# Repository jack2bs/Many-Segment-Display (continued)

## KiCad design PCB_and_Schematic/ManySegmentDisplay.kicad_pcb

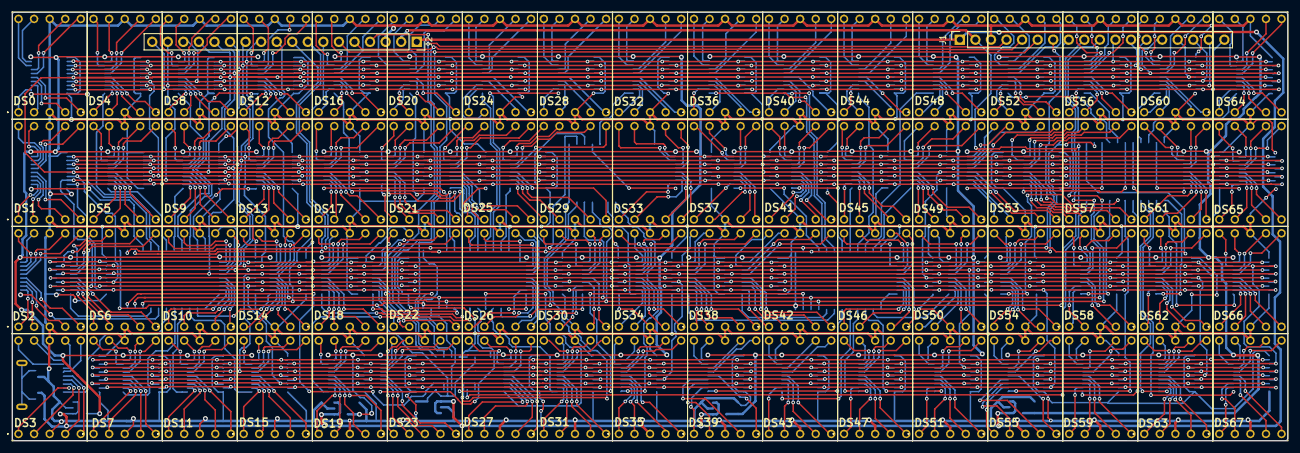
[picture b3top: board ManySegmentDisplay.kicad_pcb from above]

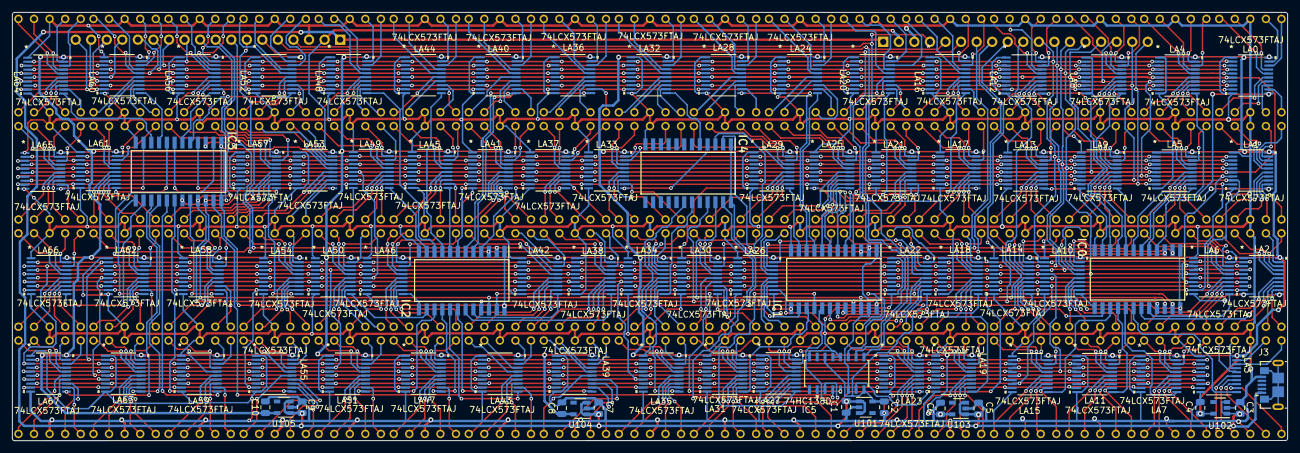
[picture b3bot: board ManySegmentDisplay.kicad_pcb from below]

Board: 2 copper layers, 208.1 x 69.9 mm, 160 parts (90 on the bottom side), 636 nets.

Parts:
C1, C2, C3, C4, C5, C6, C7, C8, C9, C10: 1uF; C_0805_2012Metric
DS0, DS1, DS2, DS3, DS4, DS5, DS6, DS7, DS8, DS9, DS10, DS11, DS12, DS13, DS14, DS15, DS16, DS17, DS18, DS19, DS20, DS21, DS22, DS23, DS24, DS25, DS26, DS27, DS28, DS29, DS30, DS31, DS32, DS33, DS34, DS35, DS36, DS37, DS38, DS39, DS40, DS41, DS42, DS43, DS44, DS45, DS46, DS47, DS48, DS49, DS50, DS51, DS52, DS53, DS54, DS55, DS56, DS57, DS58, DS59, DS60, DS61, DS62, DS63, DS64, DS65, DS66, DS67: TDSR1360-IK; TDSR1360IK
IC0, IC1, IC2, IC3, IC4: 74HC4514D,653; SOIC127P1032X265-24N
IC5: 74HC138D
J1, J2: ManySegDisplayConn; PinSocket_1x18_P2.54mm_Vertical
J3: USB_B_Micro; USB_Micro-B_GCT_USB3076-30-A
LA0, LA1, LA2, LA3, LA4, LA5, LA6, LA7, LA8, LA9, LA10, LA11, LA12, LA13, LA14, LA15, LA16, LA17, LA18, LA19, LA20, LA21, LA22, LA23, LA24, LA25, LA26, LA27, LA28, LA29, LA30, LA31, LA32, LA33, LA34, LA35, LA36, LA37, LA38, LA39, LA40, LA41, LA42, LA43, LA44, LA45, LA46, LA47, LA48, LA49, LA50, LA51, LA52, LA53, LA54, LA55, LA56, LA57, LA58, LA59, LA60, LA61, LA62, LA63, LA64, LA65, LA66, LA67: 74LCX573FTAJ
U101, U102, U103, U104, U105: TPS73133DBV; SOT-23-5

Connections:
+1V8: C4.1, C6.1, C8.1, C10.1, LA0.20, LA1.20, LA2.20, LA3.20, LA4.20, LA5.20, LA6.20, LA7.20, LA8.20, LA9.20, LA10.20, LA11.20, LA12.20, LA13.20, LA14.20, LA15.20, LA16.20, LA17.20, LA18.20, LA19.20, LA20.20, LA21.20, LA22.20, LA23.20, LA24.20, LA25.20, LA26.20, LA27.20, LA28.20, LA29.20, LA30.20, LA31.20, LA32.20, LA33.20, LA34.20, LA35.20, LA36.20, LA37.20, LA38.20, LA39.20, LA40.20, LA41.20, LA42.20, LA43.20, LA44.20, LA45.20, LA46.20, LA47.20, LA48.20, LA49.20, LA50.20, LA51.20, LA52.20, LA53.20, LA54.20, LA55.20, LA56.20, LA57.20, LA58.20, LA59.20, LA60.20, LA61.20, LA62.20, LA63.20, LA64.20, LA65.20, LA66.20, LA67.20, U102.5, U103.5, U104.5, U105.5
+3V3: C2.1, IC0.1, IC0.24, IC1.1, IC1.24, IC2.1, IC2.24, IC3.1, IC3.24, IC4.1, IC4.24, IC5.6, IC5.16, J1.2, J2.2, U101.5
+5V: C1.1, C3.1, C5.1, C7.1, C9.1, J1.1, J2.1, J3.1, U101.1, U101.3, U102.1, U102.3, U103.1, U103.3, U104.1, U104.3, U105.1, U105.3
AD0: IC5.1, J1.4, J2.4
AD1: IC5.2, J1.5, J2.5
AD2: IC5.3, J1.6, J2.6
AD3: IC0.2, IC1.2, IC2.2, IC3.2, IC4.2, J1.7, J2.7
AD4: IC0.3, IC1.3, IC2.3, IC3.3, IC4.3, J1.8, J2.8
AD5: IC0.21, IC1.21, IC2.21, IC3.21, IC4.21, J1.9, J2.9
AD6: IC0.22, IC1.22, IC2.22, IC3.22, IC4.22, J1.10, J2.10
D1A: IC0.13, LA10.11
D1B: IC0.16, LA11.11
D1C: IC0.10, LA12.11
D1D: IC0.11, LA13.11
D1E: IC0.14, LA14.11
D1F: IC0.15, LA15.11
D2A: IC1.13, LA26.11
D2B: IC1.16, LA27.11
D2C: IC1.10, LA28.11
D2D: IC1.11, LA29.11
D2E: IC1.14, LA30.11
D2F: IC1.15, LA31.11
D3A: IC2.13, LA46.11
D3B: IC2.16, LA47.11
D3C: IC2.10, LA48.11
D3D: IC2.11, LA49.11
D3E: IC2.14, LA50.11
D3F: IC2.15, LA51.11
D4A: IC3.13, LA62.11
D4B: IC3.16, LA63.11
D4C: IC3.10, LA64.11
D4D: IC3.11, LA65.11
D4E: IC3.14, LA66.11
D4F: IC3.15, LA67.11
D10: IC0.5, LA0.11
D11: IC0.4, LA1.11
D12: IC0.19, LA2.11
D13: IC0.18, LA3.11
D14: IC0.6, LA4.11
D15: IC0.7, LA5.11
D16: IC0.20, LA6.11
D17: IC0.17, LA7.11
D18: IC0.9, LA8.11
D19: IC0.8, LA9.11
D20: IC1.5, LA16.11
D21: IC1.4, LA17.11
D22: IC1.19, LA18.11
D23: IC1.18, LA19.11
D24: IC1.6, LA20.11
D25: IC1.7, LA21.11
D26: IC1.20, LA22.11
D27: IC1.17, LA23.11
D28: IC1.9, LA24.11
D29: IC1.8, LA25.11
D30: IC2.5, LA36.11
D31: IC2.4, LA37.11
D32: IC2.19, LA38.11
D33: IC2.18, LA39.11
D34: IC2.6, LA40.11
D35: IC2.7, LA41.11
D36: IC2.20, LA42.11
D37: IC2.17, LA43.11
D38: IC2.9, LA44.11
D39: IC2.8, LA45.11
D40: IC3.5, LA52.11
D41: IC3.4, LA53.11
D42: IC3.19, LA54.11
D43: IC3.18, LA55.11
D44: IC3.6, LA56.11
D45: IC3.7, LA57.11
D46: IC3.20, LA58.11
D47: IC3.17, LA59.11
D48: IC3.9, LA60.11
D49: IC3.8, LA61.11
D50: IC4.5, LA32.11
D51: IC4.4, LA33.11
D52: IC4.19, LA34.11
D53: IC4.18, LA35.11
GND: C1.2, C2.2, C3.2, C4.2, C5.2, C6.2, C7.2, C8.2, C9.2, C10.2, DS0.3, DS0.8, DS1.3, DS1.8, DS2.3, DS2.8, DS3.3, DS3.8, DS4.3, DS4.8, DS5.3, DS5.8, DS6.3, DS6.8, DS7.3, DS7.8, DS8.3, DS8.8, DS9.3, DS9.8, DS10.3, DS10.8, DS11.3, DS11.8, DS12.3, DS12.8, DS13.3, DS13.8, DS14.3, DS14.8, DS15.3, DS15.8, DS16.3, DS16.8, DS17.3, DS17.8, DS18.3, DS18.8, DS19.3, DS19.8, DS20.3, DS20.8, DS21.3, DS21.8, DS22.3, DS22.8, DS23.3, DS23.8, DS24.3, DS24.8, DS25.3, DS25.8, DS26.3, DS26.8, DS27.3, DS27.8, DS28.3, DS28.8, DS29.3, DS29.8, DS30.3, DS30.8, DS31.3, DS31.8, DS32.3, DS32.8, DS33.3, DS33.8, DS34.3, DS34.8, DS35.3, DS35.8, DS36.3, DS36.8, DS37.3, DS37.8, DS38.3, DS38.8, DS39.3, DS39.8, DS40.3, DS40.8, DS41.3, DS41.8, DS42.3, DS42.8, DS43.3, DS43.8, DS44.3, DS44.8, DS45.3, DS45.8, DS46.3, DS46.8, DS47.3, DS47.8, DS48.3, DS48.8, DS49.3, DS49.8, DS50.3, DS50.8, DS51.3, DS51.8, DS52.3, DS52.8, DS53.3, DS53.8, DS54.3, DS54.8, DS55.3, DS55.8, DS56.3, DS56.8, DS57.3, DS57.8, DS58.3, DS58.8, DS59.3, DS59.8, DS60.3, DS60.8, DS61.3, DS61.8, DS62.3, DS62.8, DS63.3, DS63.8, DS64.3, DS64.8, DS65.3, DS65.8, DS66.3, DS66.8, DS67.3, DS67.8, IC0.12, IC1.12, IC2.12, IC3.12, IC4.12, IC5.4, IC5.5, IC5.8, J1.3, J2.3, J3.5, LA0.1, LA0.10, LA1.1, LA1.10, LA2.1, LA2.10, LA3.1, LA3.10, LA4.1, LA4.10, LA5.1, LA5.10, LA6.1, LA6.10, LA7.1, LA7.10, LA8.1, LA8.10, LA9.1, LA9.10, LA10.1, LA10.10, LA11.1, LA11.10, LA12.1, LA12.10, LA13.1, LA13.10, LA14.1, LA14.10, LA15.1, LA15.10, LA16.1, LA16.10, LA17.1, LA17.10, LA18.1, LA18.10, LA19.1, LA19.10, LA20.1, LA20.10, LA21.1, LA21.10, LA22.1, LA22.10, LA23.1, LA23.10, LA24.1, LA24.10, LA25.1, LA25.10, LA26.1, LA26.10, LA27.1, LA27.10, LA28.1, LA28.10, LA29.1, LA29.10, LA30.1, LA30.10, LA31.1, LA31.10, LA32.1, LA32.10, LA33.1, LA33.10, LA34.1, LA34.10, LA35.1, LA35.10, LA36.1, LA36.10, LA37.1, LA37.10, LA38.1, LA38.10, LA39.1, LA39.10, LA40.1, LA40.10, LA41.1, LA41.10, LA42.1, LA42.10, LA43.1, LA43.10, LA44.1, LA44.10, LA45.1, LA45.10, LA46.1, LA46.10, LA47.1, LA47.10, LA48.1, LA48.10, LA49.1, LA49.10, LA50.1, LA50.10, LA51.1, LA51.10, LA52.1, LA52.10, LA53.1, LA53.10, LA54.1, LA54.10, LA55.1, LA55.10, LA56.1, LA56.10, LA57.1, LA57.10, LA58.1, LA58.10, LA59.1, LA59.10, LA60.1, LA60.10, LA61.1, LA61.10, LA62.1, LA62.10, LA63.1, LA63.10, LA64.1, LA64.10, LA65.1, LA65.10, LA66.1, LA66.10, LA67.1, LA67.10, U101.2, U102.2, U103.2, U104.2, U105.2
unnamed: DS0.1, LA0.12
unnamed: DS0.2, LA0.13
unnamed: DS0.4, LA0.14
unnamed: DS0.5, LA0.15
unnamed: DS0.6, LA0.16
unnamed: DS0.7, LA0.17
unnamed: DS0.9, LA0.19
unnamed: DS0.10, LA0.18
unnamed: DS1.1, LA1.12
unnamed: DS1.2, LA1.13
unnamed: DS1.4, LA1.14
unnamed: DS1.5, LA1.15
unnamed: DS1.6, LA1.16
unnamed: DS1.7, LA1.17
unnamed: DS1.9, LA1.19
unnamed: DS1.10, LA1.18
unnamed: DS2.1, LA2.12
unnamed: DS2.2, LA2.13
unnamed: DS2.4, LA2.14
unnamed: DS2.5, LA2.15
unnamed: DS2.6, LA2.16
unnamed: DS2.7, LA2.17
unnamed: DS2.9, LA2.19
unnamed: DS2.10, LA2.18
unnamed: DS3.1, LA3.12
unnamed: DS3.2, LA3.13
unnamed: DS3.4, LA3.14
unnamed: DS3.5, LA3.15
unnamed: DS3.6, LA3.16
unnamed: DS3.7, LA3.17
unnamed: DS3.9, LA3.19
unnamed: DS3.10, LA3.18
unnamed: DS4.1, LA4.12
unnamed: DS4.2, LA4.13
unnamed: DS4.4, LA4.14
unnamed: DS4.5, LA4.15
unnamed: DS4.6, LA4.16
unnamed: DS4.7, LA4.17
unnamed: DS4.9, LA4.19
unnamed: DS4.10, LA4.18
unnamed: DS5.1, LA5.12
unnamed: DS5.2, LA5.13
unnamed: DS5.4, LA5.14
unnamed: DS5.5, LA5.15
unnamed: DS5.6, LA5.16
unnamed: DS5.7, LA5.17
unnamed: DS5.9, LA5.19
unnamed: DS5.10, LA5.18
unnamed: DS6.1, LA6.12
unnamed: DS6.2, LA6.13
unnamed: DS6.4, LA6.14
unnamed: DS6.5, LA6.15
unnamed: DS6.6, LA6.16
unnamed: DS6.7, LA6.17
unnamed: DS6.9, LA6.19
unnamed: DS6.10, LA6.18
unnamed: DS7.1, LA7.12
unnamed: DS7.2, LA7.13
unnamed: DS7.4, LA7.14
unnamed: DS7.5, LA7.15
unnamed: DS7.6, LA7.16
unnamed: DS7.7, LA7.17
unnamed: DS7.9, LA7.19
unnamed: DS7.10, LA7.18
unnamed: DS8.1, LA8.12
unnamed: DS8.2, LA8.13
unnamed: DS8.4, LA8.14
unnamed: DS8.5, LA8.15
unnamed: DS8.6, LA8.16
unnamed: DS8.7, LA8.17
unnamed: DS8.9, LA8.19
unnamed: DS8.10, LA8.18
unnamed: DS9.1, LA9.12
unnamed: DS9.2, LA9.13
unnamed: DS9.4, LA9.14
unnamed: DS9.5, LA9.15
unnamed: DS9.6, LA9.16
unnamed: DS9.7, LA9.17
unnamed: DS9.9, LA9.19
unnamed: DS9.10, LA9.18
unnamed: DS10.1, LA10.12
unnamed: DS10.2, LA10.13
unnamed: DS10.4, LA10.14
unnamed: DS10.5, LA10.15
unnamed: DS10.6, LA10.16
unnamed: DS10.7, LA10.17
unnamed: DS10.9, LA10.19
unnamed: DS10.10, LA10.18
unnamed: DS11.1, LA11.12
unnamed: DS11.2, LA11.13
unnamed: DS11.4, LA11.14
unnamed: DS11.5, LA11.15
unnamed: DS11.6, LA11.16
unnamed: DS11.7, LA11.17
unnamed: DS11.9, LA11.19
unnamed: DS11.10, LA11.18
unnamed: DS12.1, LA12.12
unnamed: DS12.2, LA12.13
unnamed: DS12.4, LA12.14
unnamed: DS12.5, LA12.15
unnamed: DS12.6, LA12.16
unnamed: DS12.7, LA12.17
unnamed: DS12.9, LA12.19
unnamed: DS12.10, LA12.18
unnamed: DS13.1, LA13.12
unnamed: DS13.2, LA13.13
unnamed: DS13.4, LA13.14
unnamed: DS13.5, LA13.15
unnamed: DS13.6, LA13.16
unnamed: DS13.7, LA13.17
unnamed: DS13.9, LA13.19
unnamed: DS13.10, LA13.18
unnamed: DS14.1, LA14.12
unnamed: DS14.2, LA14.13
unnamed: DS14.4, LA14.14
unnamed: DS14.5, LA14.15
unnamed: DS14.6, LA14.16
unnamed: DS14.7, LA14.17
unnamed: DS14.9, LA14.19
unnamed: DS14.10, LA14.18
unnamed: DS15.1, LA15.12
unnamed: DS15.2, LA15.13
unnamed: DS15.4, LA15.14
unnamed: DS15.5, LA15.15
unnamed: DS15.6, LA15.16
unnamed: DS15.7, LA15.17
unnamed: DS15.9, LA15.19
unnamed: DS15.10, LA15.18
unnamed: DS16.1, LA16.12
unnamed: DS16.2, LA16.13
unnamed: DS16.4, LA16.14
unnamed: DS16.5, LA16.15
unnamed: DS16.6, LA16.16
unnamed: DS16.7, LA16.17
unnamed: DS16.9, LA16.19
unnamed: DS16.10, LA16.18
unnamed: DS17.1, LA17.12
unnamed: DS17.2, LA17.13
unnamed: DS17.4, LA17.14
unnamed: DS17.5, LA17.15
unnamed: DS17.6, LA17.16
unnamed: DS17.7, LA17.17
unnamed: DS17.9, LA17.19
unnamed: DS17.10, LA17.18
unnamed: DS18.1, LA18.12
unnamed: DS18.2, LA18.13
unnamed: DS18.4, LA18.14
unnamed: DS18.5, LA18.15
unnamed: DS18.6, LA18.16
unnamed: DS18.7, LA18.17
unnamed: DS18.9, LA18.19
unnamed: DS18.10, LA18.18
unnamed: DS19.1, LA19.12
unnamed: DS19.2, LA19.13
unnamed: DS19.4, LA19.14
unnamed: DS19.5, LA19.15
unnamed: DS19.6, LA19.16
unnamed: DS19.7, LA19.17
unnamed: DS19.9, LA19.19
unnamed: DS19.10, LA19.18
unnamed: DS20.1, LA20.12
unnamed: DS20.2, LA20.13
unnamed: DS20.4, LA20.14
unnamed: DS20.5, LA20.15
unnamed: DS20.6, LA20.16
unnamed: DS20.7, LA20.17
unnamed: DS20.9, LA20.19
unnamed: DS20.10, LA20.18
unnamed: DS21.1, LA21.12
unnamed: DS21.2, LA21.13
unnamed: DS21.4, LA21.14
unnamed: DS21.5, LA21.15
unnamed: DS21.6, LA21.16
unnamed: DS21.7, LA21.17
unnamed: DS21.9, LA21.19
unnamed: DS21.10, LA21.18
unnamed: DS22.1, LA22.12
unnamed: DS22.2, LA22.13
unnamed: DS22.4, LA22.14
unnamed: DS22.5, LA22.15
unnamed: DS22.6, LA22.16
unnamed: DS22.7, LA22.17
unnamed: DS22.9, LA22.19
unnamed: DS22.10, LA22.18
unnamed: DS23.1, LA23.12
unnamed: DS23.2, LA23.13
unnamed: DS23.4, LA23.14
unnamed: DS23.5, LA23.15
unnamed: DS23.6, LA23.16
unnamed: DS23.7, LA23.17
unnamed: DS23.9, LA23.19
unnamed: DS23.10, LA23.18
unnamed: DS24.1, LA24.12
unnamed: DS24.2, LA24.13
unnamed: DS24.4, LA24.14
unnamed: DS24.5, LA24.15
unnamed: DS24.6, LA24.16
unnamed: DS24.7, LA24.17
unnamed: DS24.9, LA24.19
unnamed: DS24.10, LA24.18
unnamed: DS25.1, LA25.12
unnamed: DS25.2, LA25.13
unnamed: DS25.4, LA25.14
unnamed: DS25.5, LA25.15
unnamed: DS25.6, LA25.16
unnamed: DS25.7, LA25.17
unnamed: DS25.9, LA25.19
unnamed: DS25.10, LA25.18
unnamed: DS26.1, LA26.12
unnamed: DS26.2, LA26.13
unnamed: DS26.4, LA26.14
unnamed: DS26.5, LA26.15
unnamed: DS26.6, LA26.16
unnamed: DS26.7, LA26.17
unnamed: DS26.9, LA26.19
unnamed: DS26.10, LA26.18
unnamed: DS27.1, LA27.12
unnamed: DS27.2, LA27.13
unnamed: DS27.4, LA27.14
unnamed: DS27.5, LA27.15
unnamed: DS27.6, LA27.16
unnamed: DS27.7, LA27.17
unnamed: DS27.9, LA27.19
unnamed: DS27.10, LA27.18
unnamed: DS28.1, LA28.12
unnamed: DS28.2, LA28.13
unnamed: DS28.4, LA28.14
unnamed: DS28.5, LA28.15
unnamed: DS28.6, LA28.16
unnamed: DS28.7, LA28.17
unnamed: DS28.9, LA28.19
unnamed: DS28.10, LA28.18
unnamed: DS29.1, LA29.12
unnamed: DS29.2, LA29.13
unnamed: DS29.4, LA29.14
unnamed: DS29.5, LA29.15
unnamed: DS29.6, LA29.16
unnamed: DS29.7, LA29.17
unnamed: DS29.9, LA29.19
unnamed: DS29.10, LA29.18
unnamed: DS30.1, LA30.12
unnamed: DS30.2, LA30.13
unnamed: DS30.4, LA30.14
unnamed: DS30.5, LA30.15
unnamed: DS30.6, LA30.16
unnamed: DS30.7, LA30.17
unnamed: DS30.9, LA30.19
unnamed: DS30.10, LA30.18
unnamed: DS31.1, LA31.12
unnamed: DS31.2, LA31.13
unnamed: DS31.4, LA31.14
unnamed: DS31.5, LA31.15
unnamed: DS31.6, LA31.16
unnamed: DS31.7, LA31.17
unnamed: DS31.9, LA31.19
unnamed: DS31.10, LA31.18
unnamed: DS32.1, LA32.12
unnamed: DS32.2, LA32.13
unnamed: DS32.4, LA32.14
unnamed: DS32.5, LA32.15
unnamed: DS32.6, LA32.16
unnamed: DS32.7, LA32.17
unnamed: DS32.9, LA32.19
unnamed: DS32.10, LA32.18
unnamed: DS33.1, LA33.12
unnamed: DS33.2, LA33.13
unnamed: DS33.4, LA33.14
unnamed: DS33.5, LA33.15
unnamed: DS33.6, LA33.16
unnamed: DS33.7, LA33.17
unnamed: DS33.9, LA33.19
unnamed: DS33.10, LA33.18
unnamed: DS34.1, LA34.12
unnamed: DS34.2, LA34.13
unnamed: DS34.4, LA34.14
unnamed: DS34.5, LA34.15
unnamed: DS34.6, LA34.16
unnamed: DS34.7, LA34.17
unnamed: DS34.9, LA34.19
unnamed: DS34.10, LA34.18
unnamed: DS35.1, LA35.12
unnamed: DS35.2, LA35.13
unnamed: DS35.4, LA35.14
unnamed: DS35.5, LA35.15
unnamed: DS35.6, LA35.16
unnamed: DS35.7, LA35.17
unnamed: DS35.9, LA35.19
unnamed: DS35.10, LA35.18
unnamed: DS36.1, LA36.12
unnamed: DS36.2, LA36.13
unnamed: DS36.4, LA36.14
unnamed: DS36.5, LA36.15
unnamed: DS36.6, LA36.16
unnamed: DS36.7, LA36.17
unnamed: DS36.9, LA36.19
unnamed: DS36.10, LA36.18
unnamed: DS37.1, LA37.12
unnamed: DS37.2, LA37.13
unnamed: DS37.4, LA37.14
unnamed: DS37.5, LA37.15
unnamed: DS37.6, LA37.16
unnamed: DS37.7, LA37.17
unnamed: DS37.9, LA37.19
unnamed: DS37.10, LA37.18
unnamed: DS38.1, LA38.12
unnamed: DS38.2, LA38.13
unnamed: DS38.4, LA38.14
unnamed: DS38.5, LA38.15
unnamed: DS38.6, LA38.16
unnamed: DS38.7, LA38.17
unnamed: DS38.9, LA38.19
unnamed: DS38.10, LA38.18
unnamed: DS39.1, LA39.12
unnamed: DS39.2, LA39.13
unnamed: DS39.4, LA39.14
unnamed: DS39.5, LA39.15
unnamed: DS39.6, LA39.16
unnamed: DS39.7, LA39.17
unnamed: DS39.9, LA39.19
unnamed: DS39.10, LA39.18
unnamed: DS40.1, LA40.12
unnamed: DS40.2, LA40.13
unnamed: DS40.4, LA40.14
unnamed: DS40.5, LA40.15
unnamed: DS40.6, LA40.16
unnamed: DS40.7, LA40.17
unnamed: DS40.9, LA40.19
unnamed: DS40.10, LA40.18
unnamed: DS41.1, LA41.12
unnamed: DS41.2, LA41.13
unnamed: DS41.4, LA41.14
unnamed: DS41.5, LA41.15
unnamed: DS41.6, LA41.16
unnamed: DS41.7, LA41.17
unnamed: DS41.9, LA41.19
unnamed: DS41.10, LA41.18
unnamed: DS42.1, LA42.12
unnamed: DS42.2, LA42.13
unnamed: DS42.4, LA42.14
unnamed: DS42.5, LA42.15
unnamed: DS42.6, LA42.16
unnamed: DS42.7, LA42.17
unnamed: DS42.9, LA42.19
unnamed: DS42.10, LA42.18
unnamed: DS43.1, LA43.12
unnamed: DS43.2, LA43.13
unnamed: DS43.4, LA43.14
unnamed: DS43.5, LA43.15
unnamed: DS43.6, LA43.16
unnamed: DS43.7, LA43.17
unnamed: DS43.9, LA43.19
unnamed: DS43.10, LA43.18
unnamed: DS44.1, LA44.12
unnamed: DS44.2, LA44.13
unnamed: DS44.4, LA44.14
unnamed: DS44.5, LA44.15
unnamed: DS44.6, LA44.16
unnamed: DS44.7, LA44.17
unnamed: DS44.9, LA44.19
unnamed: DS44.10, LA44.18
unnamed: DS45.1, LA45.12
unnamed: DS45.2, LA45.13
unnamed: DS45.4, LA45.14
unnamed: DS45.5, LA45.15
unnamed: DS45.6, LA45.16
unnamed: DS45.7, LA45.17
unnamed: DS45.9, LA45.19
unnamed: DS45.10, LA45.18
unnamed: DS46.1, LA46.12
unnamed: DS46.2, LA46.13
unnamed: DS46.4, LA46.14
unnamed: DS46.5, LA46.15
unnamed: DS46.6, LA46.16
unnamed: DS46.7, LA46.17
unnamed: DS46.9, LA46.19
unnamed: DS46.10, LA46.18
unnamed: DS47.1, LA47.12
unnamed: DS47.2, LA47.13
unnamed: DS47.4, LA47.14
unnamed: DS47.5, LA47.15
unnamed: DS47.6, LA47.16
unnamed: DS47.7, LA47.17
unnamed: DS47.9, LA47.19
unnamed: DS47.10, LA47.18
unnamed: DS48.1, LA48.12
unnamed: DS48.2, LA48.13
unnamed: DS48.4, LA48.14
unnamed: DS48.5, LA48.15
unnamed: DS48.6, LA48.16
unnamed: DS48.7, LA48.17
unnamed: DS48.9, LA48.19
unnamed: DS48.10, LA48.18
unnamed: DS49.1, LA49.12
unnamed: DS49.2, LA49.13
unnamed: DS49.4, LA49.14
unnamed: DS49.5, LA49.15
unnamed: DS49.6, LA49.16
unnamed: DS49.7, LA49.17
unnamed: DS49.9, LA49.19
unnamed: DS49.10, LA49.18
unnamed: DS50.1, LA50.12
unnamed: DS50.2, LA50.13
unnamed: DS50.4, LA50.14
unnamed: DS50.5, LA50.15
unnamed: DS50.6, LA50.16
unnamed: DS50.7, LA50.17
unnamed: DS50.9, LA50.19
unnamed: DS50.10, LA50.18
unnamed: DS51.1, LA51.12
unnamed: DS51.2, LA51.13
unnamed: DS51.4, LA51.14
unnamed: DS51.5, LA51.15
unnamed: DS51.6, LA51.16
unnamed: DS51.7, LA51.17
unnamed: DS51.9, LA51.19
unnamed: DS51.10, LA51.18
unnamed: DS52.1, LA52.12
unnamed: DS52.2, LA52.13
unnamed: DS52.4, LA52.14
unnamed: DS52.5, LA52.15
unnamed: DS52.6, LA52.16
unnamed: DS52.7, LA52.17
unnamed: DS52.9, LA52.19
unnamed: DS52.10, LA52.18
unnamed: DS53.1, LA53.12
unnamed: DS53.2, LA53.13
unnamed: DS53.4, LA53.14
unnamed: DS53.5, LA53.15
unnamed: DS53.6, LA53.16
unnamed: DS53.7, LA53.17
unnamed: DS53.9, LA53.19
unnamed: DS53.10, LA53.18
unnamed: DS54.1, LA54.12
unnamed: DS54.2, LA54.13
unnamed: DS54.4, LA54.14
unnamed: DS54.5, LA54.15
unnamed: DS54.6, LA54.16
unnamed: DS54.7, LA54.17
unnamed: DS54.9, LA54.19
unnamed: DS54.10, LA54.18
unnamed: DS55.1, LA55.12
unnamed: DS55.2, LA55.13
unnamed: DS55.4, LA55.14
unnamed: DS55.5, LA55.15
unnamed: DS55.6, LA55.16
unnamed: DS55.7, LA55.17
unnamed: DS55.9, LA55.19
unnamed: DS55.10, LA55.18
unnamed: DS56.1, LA56.12
unnamed: DS56.2, LA56.13
unnamed: DS56.4, LA56.14
unnamed: DS56.5, LA56.15
unnamed: DS56.6, LA56.16
unnamed: DS56.7, LA56.17
unnamed: DS56.9, LA56.19
unnamed: DS56.10, LA56.18
unnamed: DS57.1, LA57.12
unnamed: DS57.2, LA57.13
unnamed: DS57.4, LA57.14
unnamed: DS57.5, LA57.15
unnamed: DS57.6, LA57.16
unnamed: DS57.7, LA57.17
unnamed: DS57.9, LA57.19
unnamed: DS57.10, LA57.18
unnamed: DS58.1, LA58.12
unnamed: DS58.2, LA58.13
unnamed: DS58.4, LA58.14
unnamed: DS58.5, LA58.15
unnamed: DS58.6, LA58.16
unnamed: DS58.7, LA58.17
unnamed: DS58.9, LA58.19
unnamed: DS58.10, LA58.18
unnamed: DS59.1, LA59.12
unnamed: DS59.2, LA59.13
unnamed: DS59.4, LA59.14
unnamed: DS59.5, LA59.15
unnamed: DS59.6, LA59.16
unnamed: DS59.7, LA59.17
unnamed: DS59.9, LA59.19
unnamed: DS59.10, LA59.18
unnamed: DS60.1, LA60.12
unnamed: DS60.2, LA60.13
unnamed: DS60.4, LA60.14
unnamed: DS60.5, LA60.15
unnamed: DS60.6, LA60.16
unnamed: DS60.7, LA60.17
unnamed: DS60.9, LA60.19
unnamed: DS60.10, LA60.18
unnamed: DS61.1, LA61.12
unnamed: DS61.2, LA61.13
unnamed: DS61.4, LA61.14
unnamed: DS61.5, LA61.15
unnamed: DS61.6, LA61.16
unnamed: DS61.7, LA61.17
unnamed: DS61.9, LA61.19
unnamed: DS61.10, LA61.18
unnamed: DS62.1, LA62.12
unnamed: DS62.2, LA62.13
unnamed: DS62.4, LA62.14
unnamed: DS62.5, LA62.15
unnamed: DS62.6, LA62.16
unnamed: DS62.7, LA62.17
unnamed: DS62.9, LA62.19
unnamed: DS62.10, LA62.18
unnamed: DS63.1, LA63.12
unnamed: DS63.2, LA63.13
unnamed: DS63.4, LA63.14
unnamed: DS63.5, LA63.15
unnamed: DS63.6, LA63.16
unnamed: DS63.7, LA63.17
unnamed: DS63.9, LA63.19
unnamed: DS63.10, LA63.18
unnamed: DS64.1, LA64.12
unnamed: DS64.2, LA64.13
unnamed: DS64.4, LA64.14
unnamed: DS64.5, LA64.15
unnamed: DS64.6, LA64.16
unnamed: DS64.7, LA64.17
unnamed: DS64.9, LA64.19
unnamed: DS64.10, LA64.18
unnamed: DS65.1, LA65.12
unnamed: DS65.2, LA65.13
unnamed: DS65.4, LA65.14
unnamed: DS65.5, LA65.15
unnamed: DS65.6, LA65.16
unnamed: DS65.7, LA65.17
unnamed: DS65.9, LA65.19
unnamed: DS65.10, LA65.18
unnamed: DS66.1, LA66.12
unnamed: DS66.2, LA66.13
unnamed: DS66.4, LA66.14
unnamed: DS66.5, LA66.15
unnamed: DS66.6, LA66.16
unnamed: DS66.7, LA66.17
unnamed: DS66.9, LA66.19
unnamed: DS66.10, LA66.18
unnamed: DS67.1, LA67.12
unnamed: DS67.2, LA67.13
unnamed: DS67.4, LA67.14
unnamed: DS67.5, LA67.15
unnamed: DS67.6, LA67.16
unnamed: DS67.7, LA67.17
unnamed: DS67.9, LA67.19
unnamed: DS67.10, LA67.18
unnamed: IC0.23, IC5.15
unnamed: IC1.23, IC5.14
unnamed: IC2.23, IC5.13
unnamed: IC3.23, IC5.12
unnamed: IC4.23, IC5.11
PA0: J1.11, J2.11, LA0.2, LA1.2, LA2.2, LA3.2, LA4.2, LA5.2, LA6.2, LA7.2, LA8.2, LA9.2, LA10.2, LA11.2, LA12.2, LA13.2, LA14.2, LA15.2, LA16.2, LA17.2, LA18.2, LA19.2, LA20.2, LA21.2, LA22.2, LA23.2, LA24.2, LA25.2, LA26.2, LA27.2, LA28.2, LA29.2, LA30.2, LA31.2, LA32.2, LA33.2, LA34.2, LA35.2, LA36.2, LA37.2, LA38.2, LA39.2, LA40.2, LA41.2, LA42.2, LA43.2, LA44.2, LA45.2, LA46.2, LA47.2, LA48.2, LA49.2, LA50.2, LA51.2, LA52.2, LA53.2, LA54.2, LA55.2, LA56.2, LA57.2, LA58.2, LA59.2, LA60.2, LA61.2, LA62.2, LA63.2, LA64.2, LA65.2, LA66.2, LA67.2
PA1: J1.12, J2.12, LA0.3, LA1.3, LA2.3, LA3.3, LA4.3, LA5.3, LA6.3, LA7.3, LA8.3, LA9.3, LA10.3, LA11.3, LA12.3, LA13.3, LA14.3, LA15.3, LA16.3, LA17.3, LA18.3, LA19.3, LA20.3, LA21.3, LA22.3, LA23.3, LA24.3, LA25.3, LA26.3, LA27.3, LA28.3, LA29.3, LA30.3, LA31.3, LA32.3, LA33.3, LA34.3, LA35.3, LA36.3, LA37.3, LA38.3, LA39.3, LA40.3, LA41.3, LA42.3, LA43.3, LA44.3, LA45.3, LA46.3, LA47.3, LA48.3, LA49.3, LA50.3, LA51.3, LA52.3, LA53.3, LA54.3, LA55.3, LA56.3, LA57.3, LA58.3, LA59.3, LA60.3, LA61.3, LA62.3, LA63.3, LA64.3, LA65.3, LA66.3, LA67.3
PA2: J1.13, J2.13, LA0.4, LA1.4, LA2.4, LA3.4, LA4.4, LA5.4, LA6.4, LA7.4, LA8.4, LA9.4, LA10.4, LA11.4, LA12.4, LA13.4, LA14.4, LA15.4, LA16.4, LA17.4, LA18.4, LA19.4, LA20.4, LA21.4, LA22.4, LA23.4, LA24.4, LA25.4, LA26.4, LA27.4, LA28.4, LA29.4, LA30.4, LA31.4, LA32.4, LA33.4, LA34.4, LA35.4, LA36.4, LA37.4, LA38.4, LA39.4, LA40.4, LA41.4, LA42.4, LA43.4, LA44.4, LA45.4, LA46.4, LA47.4, LA48.4, LA49.4, LA50.4, LA51.4, LA52.4, LA53.4, LA54.4, LA55.4, LA56.4, LA57.4, LA58.4, LA59.4, LA60.4, LA61.4, LA62.4, LA63.4, LA64.4, LA65.4, LA66.4, LA67.4
PA3: J1.14, J2.14, LA0.5, LA1.5, LA2.5, LA3.5, LA4.5, LA5.5, LA6.5, LA7.5, LA8.5, LA9.5, LA10.5, LA11.5, LA12.5, LA13.5, LA14.5, LA15.5, LA16.5, LA17.5, LA18.5, LA19.5, LA20.5, LA21.5, LA22.5, LA23.5, LA24.5, LA25.5, LA26.5, LA27.5, LA28.5, LA29.5, LA30.5, LA31.5, LA32.5, LA33.5, LA34.5, LA35.5, LA36.5, LA37.5, LA38.5, LA39.5, LA40.5, LA41.5, LA42.5, LA43.5, LA44.5, LA45.5, LA46.5, LA47.5, LA48.5, LA49.5, LA50.5, LA51.5, LA52.5, LA53.5, LA54.5, LA55.5, LA56.5, LA57.5, LA58.5, LA59.5, LA60.5, LA61.5, LA62.5, LA63.5, LA64.5, LA65.5, LA66.5, LA67.5
PA4: J1.15, J2.15, LA0.6, LA1.6, LA2.6, LA3.6, LA4.6, LA5.6, LA6.6, LA7.6, LA8.6, LA9.6, LA10.6, LA11.6, LA12.6, LA13.6, LA14.6, LA15.6, LA16.6, LA17.6, LA18.6, LA19.6, LA20.6, LA21.6, LA22.6, LA23.6, LA24.6, LA25.6, LA26.6, LA27.6, LA28.6, LA29.6, LA30.6, LA31.6, LA32.6, LA33.6, LA34.6, LA35.6, LA36.6, LA37.6, LA38.6, LA39.6, LA40.6, LA41.6, LA42.6, LA43.6, LA44.6, LA45.6, LA46.6, LA47.6, LA48.6, LA49.6, LA50.6, LA51.6, LA52.6, LA53.6, LA54.6, LA55.6, LA56.6, LA57.6, LA58.6, LA59.6, LA60.6, LA61.6, LA62.6, LA63.6, LA64.6, LA65.6, LA66.6, LA67.6
PA5: J1.16, J2.16, LA0.7, LA1.7, LA2.7, LA3.7, LA4.7, LA5.7, LA6.7, LA7.7, LA8.7, LA9.7, LA10.7, LA11.7, LA12.7, LA13.7, LA14.7, LA15.7, LA16.7, LA17.7, LA18.7, LA19.7, LA20.7, LA21.7, LA22.7, LA23.7, LA24.7, LA25.7, LA26.7, LA27.7, LA28.7, LA29.7, LA30.7, LA31.7, LA32.7, LA33.7, LA34.7, LA35.7, LA36.7, LA37.7, LA38.7, LA39.7, LA40.7, LA41.7, LA42.7, LA43.7, LA44.7, LA45.7, LA46.7, LA47.7, LA48.7, LA49.7, LA50.7, LA51.7, LA52.7, LA53.7, LA54.7, LA55.7, LA56.7, LA57.7, LA58.7, LA59.7, LA60.7, LA61.7, LA62.7, LA63.7, LA64.7, LA65.7, LA66.7, LA67.7
PA6: J1.17, J2.17, LA0.8, LA1.8, LA2.8, LA3.8, LA4.8, LA5.8, LA6.8, LA7.8, LA8.8, LA9.8, LA10.8, LA11.8, LA12.8, LA13.8, LA14.8, LA15.8, LA16.8, LA17.8, LA18.8, LA19.8, LA20.8, LA21.8, LA22.8, LA23.8, LA24.8, LA25.8, LA26.8, LA27.8, LA28.8, LA29.8, LA30.8, LA31.8, LA32.8, LA33.8, LA34.8, LA35.8, LA36.8, LA37.8, LA38.8, LA39.8, LA40.8, LA41.8, LA42.8, LA43.8, LA44.8, LA45.8, LA46.8, LA47.8, LA48.8, LA49.8, LA50.8, LA51.8, LA52.8, LA53.8, LA54.8, LA55.8, LA56.8, LA57.8, LA58.8, LA59.8, LA60.8, LA61.8, LA62.8, LA63.8, LA64.8, LA65.8, LA66.8, LA67.8
PA7: J1.18, J2.18, LA0.9, LA1.9, LA2.9, LA3.9, LA4.9, LA5.9, LA6.9, LA7.9, LA8.9, LA9.9, LA10.9, LA11.9, LA12.9, LA13.9, LA14.9, LA15.9, LA16.9, LA17.9, LA18.9, LA19.9, LA20.9, LA21.9, LA22.9, LA23.9, LA24.9, LA25.9, LA26.9, LA27.9, LA28.9, LA29.9, LA30.9, LA31.9, LA32.9, LA33.9, LA34.9, LA35.9, LA36.9, LA37.9, LA38.9, LA39.9, LA40.9, LA41.9, LA42.9, LA43.9, LA44.9, LA45.9, LA46.9, LA47.9, LA48.9, LA49.9, LA50.9, LA51.9, LA52.9, LA53.9, LA54.9, LA55.9, LA56.9, LA57.9, LA58.9, LA59.9, LA60.9, LA61.9, LA62.9, LA63.9, LA64.9, LA65.9, LA66.9, LA67.9

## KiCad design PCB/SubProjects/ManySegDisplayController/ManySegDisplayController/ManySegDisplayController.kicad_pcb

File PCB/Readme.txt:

STM32G441CBT6		https://www.newark.com/stmicroelectronics/stm32g441cbt6/mcu-32bit-170mhz-lqfp-48/dp/17AH9358

( 7 segment display:	https://www.digikey.com/en/products/detail/vishay-semiconductor-opto-division/TDSR1360-IK/4074625?s=N4IgTCBcDaIOwA4C0AVAIgZQEoEYDMAbAAxICSA0iALoC%2BQA
+ 8 bit latch:		https://www.mouser.com/ProductDetail/Toshiba/74LCX573FTAJ?qs=HXFqYaX1Q2ziMe06wbpr9A%3D%3D
)
x 100?

Temperature Sensor:	https://www.mouser.com/ProductDetail/Microchip-Technology-Atmel/AT30TSE758A-XM8M-B?qs=sGAEpiMZZMukxKgYRb08uEBhZBTtJvGT%2F6iPJE8P9E4%3D

Resistor 

4:16 decoders: 74HC4514D,653 from Nexperia Semiconductor

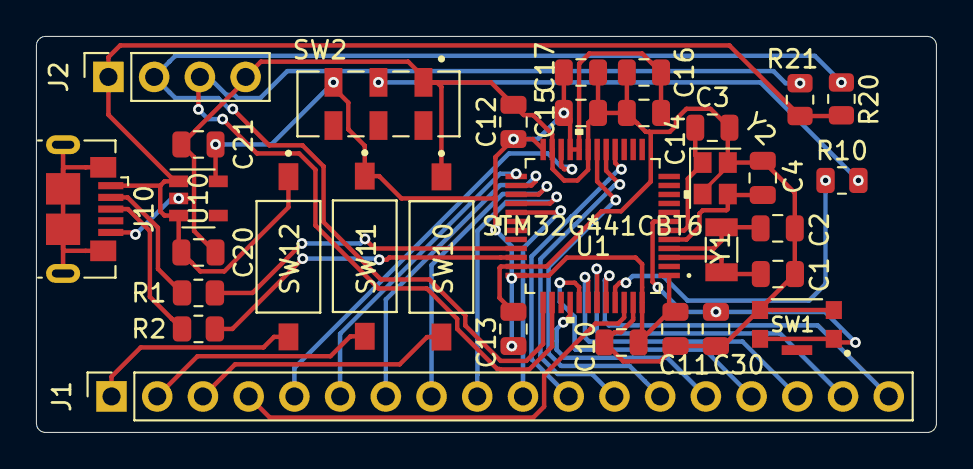
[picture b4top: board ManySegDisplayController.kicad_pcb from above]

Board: 2 copper layers, 50.0 x 22.0 mm, 32 parts (0 on the bottom side), 34 nets.

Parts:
C1, C2: 15pF; C_0805_2012Metric
C3, C4: 22pF; C_0805_2012Metric
C10: 4.7uF; C_0805_2012Metric
C11, C12, C13, C14, C30: 0.1uF; C_0805_2012Metric
C15: 10nF; C_0805_2012Metric
C16, C17: 1uF; C_0805_2012Metric
C20, C21: C_Small; C_0805_2012Metric
J1: Conn_01x18; PinSocket_1x18_P2.54mm_Vertical
J2: Conn_01x04; PinSocket_1x04_P2.54mm_Vertical
J10: USB_B_Micro; USB_Micro-B_GCT_USB3076-30-A
R1, R2: 22r; R_0805_2012Metric
R10: 10k; R_0805_2012Metric
R20, R21: R_Small; R_0805_2012Metric
SW1: SW_SPST; SW_Push_KMR421GULCLFS
SW2: SW_SPDT; SW_SPDT_JS202011JCQN
SW10, SW11, SW12: SW_SPST; SW_DIP_SPSTx01_DS04-254-2-01BK-SMT
U1: STM32G441CBT6
U10: TPS73133DBV; SOT-23-5
Y1: 32khz; Crystal_SMD_3215-2Pin_3.2x1.5mm
Y2: 16mhz; Crystal_SMD_2520-4Pin_2.5x2.0mm

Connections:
+3V3: C10.1, C11.1, C12.1, C13.1, C14.1, C15.1, C16.1, C17.1, C21.2, SW2.3, SW11.1, U1.1, U1.20, U1.21, U1.24, U1.36, U1.48, U10.5
+5V: C20.1, J2.1, J10.1, R20.1, R21.1, SW12.1, U10.1, U10.3
AD0: J1.4, U1.46
AD1: J1.5, U1.22
AD2: J1.6, U1.25
AD3: J1.7, U1.26
AD4: J1.8, U1.27
AD5: J1.9, U1.28
AD6: J1.10, U1.29
BOOT0: R10.1, U1.45
D+: R2.2, U1.34
D-: R1.2, U1.33
GND: C1.2, C2.1, C3.2, C4.2, C10.2, C11.2, C12.2, C13.2, C14.2, C15.2, C16.2, C17.2, C20.2, C21.1, C30.2, J2.4, J10.5, SW1.2, SW2.1, SW10.1, U1.19, U1.23, U1.35, U1.47, U10.2, Y2.2, Y2.4
unnamed: C1.1, U1.3, Y1.1
unnamed: C2.2, U1.4, Y1.2
unnamed: C3.1, U1.6, Y2.1
unnamed: C4.1, U1.5, Y2.3
unnamed: C30.1, SW1.1, U1.7
unnamed: J1.1, SW12.2
unnamed: J1.2, SW11.2
unnamed: J1.3, SW10.2
unnamed: J10.2, R1.1
unnamed: J10.3, R2.1
unnamed: R10.2, SW2.2
PD0: J1.11, U1.16
PD1: J1.12, U1.17
PD2: J1.13, U1.18
PD3: J1.14, U1.40
PD4: J1.15, U1.41
PD5: J1.16, U1.42
PD6: J1.17, U1.43
PD7: J1.18, U1.44
SCL: J2.2, R20.2, U1.37
SDA: J2.3, R21.2, U1.38

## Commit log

2022-06-01 Added 7seg.c and 7seg.h
2022-07-03 Not sure what changed but some stuff fs
2022-08-17 Working Version with LSI
2022-08-18 Working Version with LSE
2022-08-18 Calibration added
2022-08-19 Calibration updated
2022-08-20 Calib at 44
2022-08-21 Calib at 45
2022-10-15 Moved into Code folder
2022-10-15 Added photos
2022-10-15 Added circuit board files
2022-10-15 Removed bad readme.txt
2022-10-15 Added some photos of pcb and schematic
2022-10-15 Removed temp files
2022-10-15 added more photos
